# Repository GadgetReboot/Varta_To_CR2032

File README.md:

# Varta_To_CR2032
Use a CR2032 3V coin cell as a replacement for 3.6V Varta NiCd batteries on old motherboards.
<BR>Inspired by https://github.com/wiretap-retro/Not-A-Varta 
<br><br><br><br>

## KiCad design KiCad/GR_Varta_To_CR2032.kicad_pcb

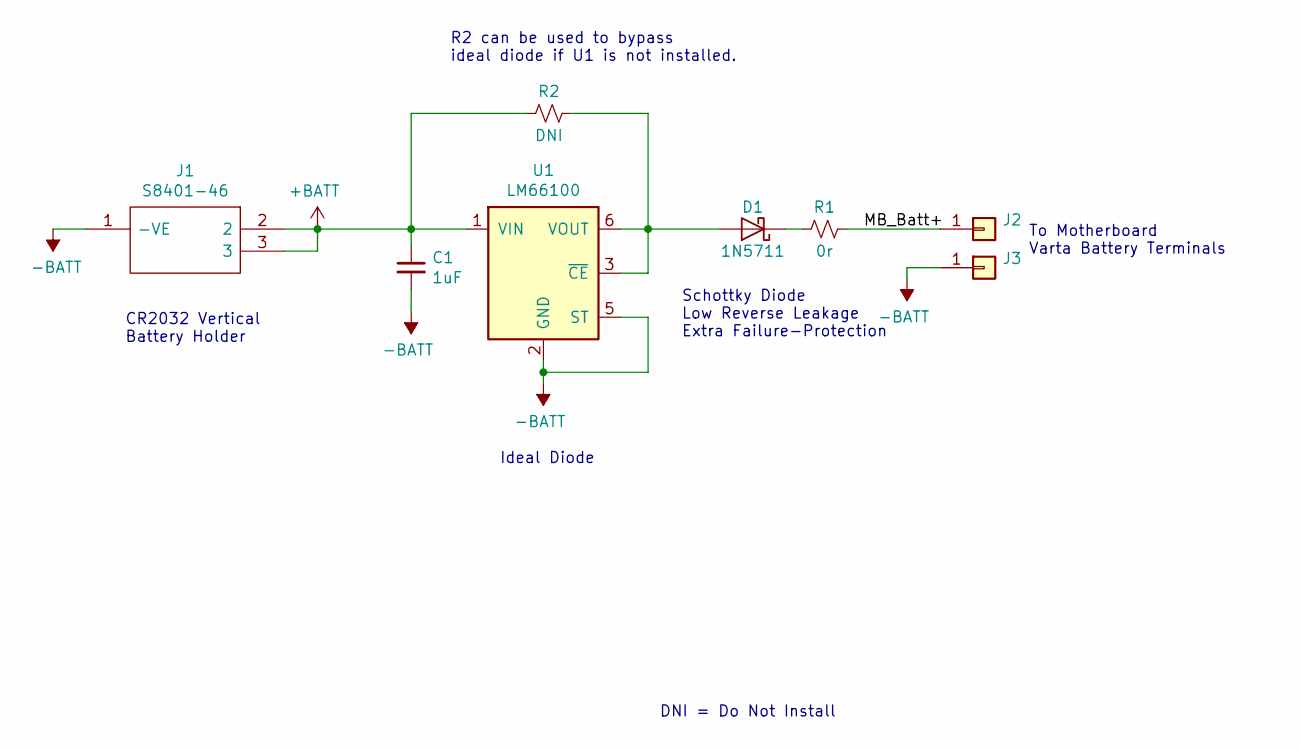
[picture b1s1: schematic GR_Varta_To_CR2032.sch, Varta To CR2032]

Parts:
C1: 1uF; C_0805_2012Metric_Pad1.15x1.40mm_HandSolder
D1: 1N5711; D_SOD-123
J1: S8401-46; Manufacturer_Part_Number S8401-46
J2, J3: Conn_01x01; PinHeader_1x01_P2.54mm_Vertical
R1: 0r; R_0805_2012Metric_Pad1.15x1.40mm_HandSolder
R2: DNI; R_0805_2012Metric_Pad1.15x1.40mm_HandSolder
U1: LM66100; SOT-363_SC-70-6_Handsoldering

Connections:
+BATT: C1.1, J1.2, J1.3, R2.2, U1.1 (VIN)
-BATT: C1.2, J1.1 (-VE), J3.1, U1.2 (GND), U1.5 (ST)
/MB_Batt+: J2.1, R1.1
unnamed: D1.1 (K), R1.2
unnamed: D1.2 (A), R2.1, U1.3 (~CE), U1.6 (VOUT)

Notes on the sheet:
Schottky Diode Low Reverse Leakage Extra Failure-Protection
CR2032 Vertical Battery Holder
To Motherboard Varta Battery Terminals
Ideal Diode
DNI = Do Not Install
R2 can be used to bypass ideal diode if U1 is not installed.

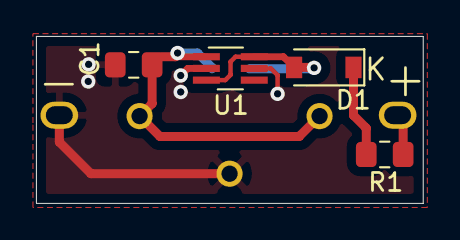
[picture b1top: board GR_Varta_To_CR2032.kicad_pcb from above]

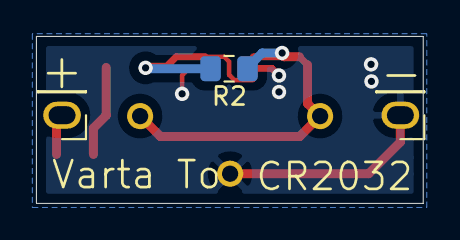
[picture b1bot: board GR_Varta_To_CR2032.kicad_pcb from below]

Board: 2 copper layers, 21.5 x 9.3 mm, 8 parts (3 on the bottom side), 5 nets.
